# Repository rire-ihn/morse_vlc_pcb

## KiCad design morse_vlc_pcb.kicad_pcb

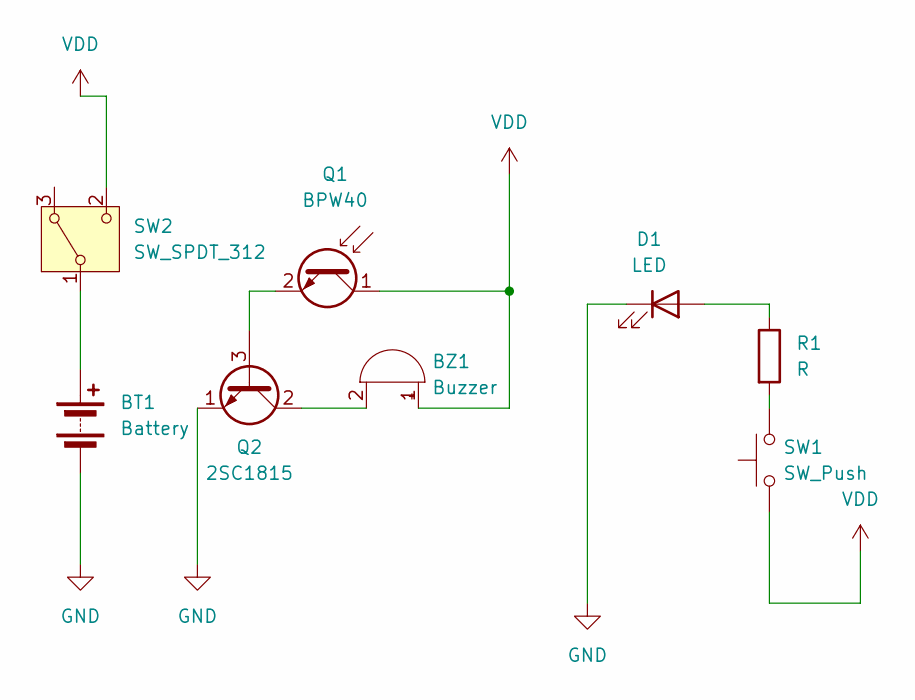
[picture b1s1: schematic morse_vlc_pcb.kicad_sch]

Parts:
BT1: Battery; cr2032_akizuki
BZ1: Buzzer; Buzzer_12x9.5RM7.6
D1: LED; LED_D3.0mm
Q1: BPW40; LED_D3.0mm
Q2: 2SC1815; TO-92_Inline_Wide
R1: R; R_Axial_DIN0207_L6.3mm_D2.5mm_P10.16mm_Horizontal
SW1: SW_Push; SW_PUSH-12mm
SW2: SW_SPDT_312; SW_Slide-03_Wuerth-WS-SLTV_10x2.5x6.4_P2.54mm

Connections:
GND: BT1.2 (-), D1.1 (K), Q2.1 (E)
unnamed: BT1.1 (+), SW2.1 (B)
unnamed: BZ1.2 (-), Q2.2 (C)
unnamed: D1.2 (A), R1.1
unnamed: Q1.2 (E), Q2.3 (B)
unnamed: R1.2, SW1.2
VDD: BZ1.1 (+), Q1.1 (C), SW1.1, SW2.2 (C)

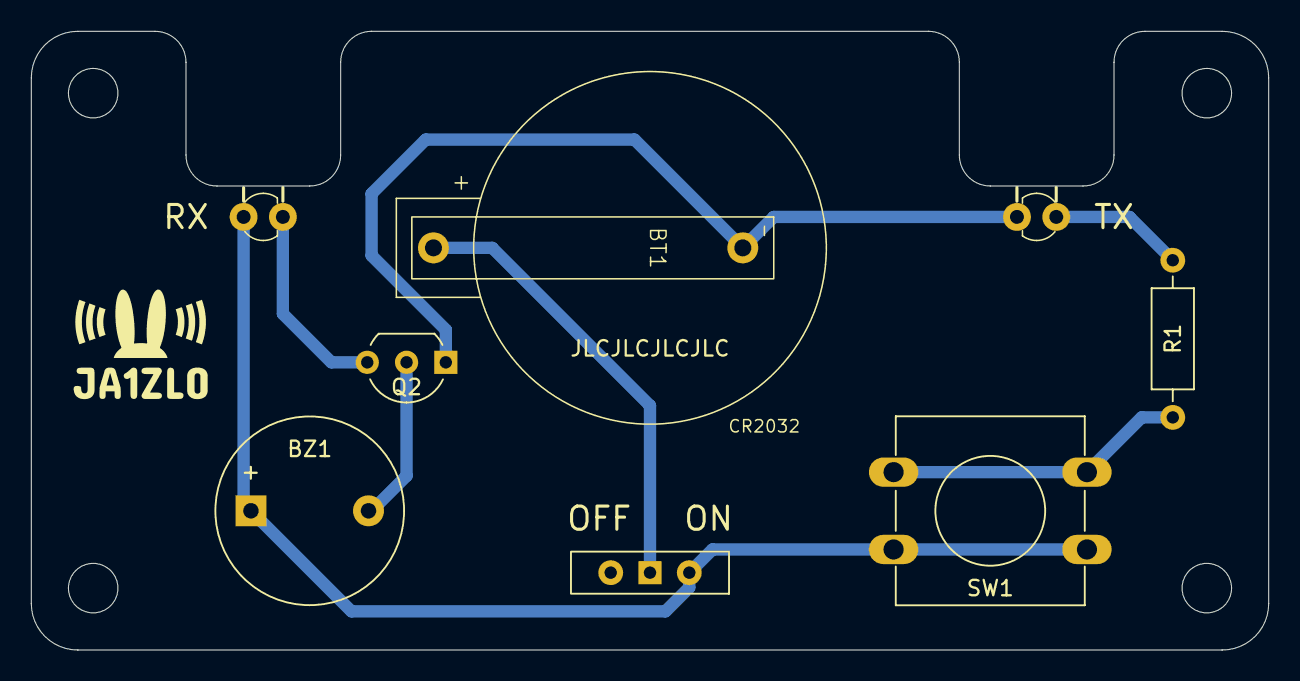
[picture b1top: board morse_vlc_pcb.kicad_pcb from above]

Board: 2 copper layers, 80.0 x 40.0 mm, 8 parts (0 on the bottom side), 7 nets.

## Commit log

2024-11-18 initial
